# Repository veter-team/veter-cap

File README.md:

Veter CAP
=============

This is eagle files to produce veter cap.

Description
-------

Complete with additional library. Designed on EAGLE 6.3 Lite.

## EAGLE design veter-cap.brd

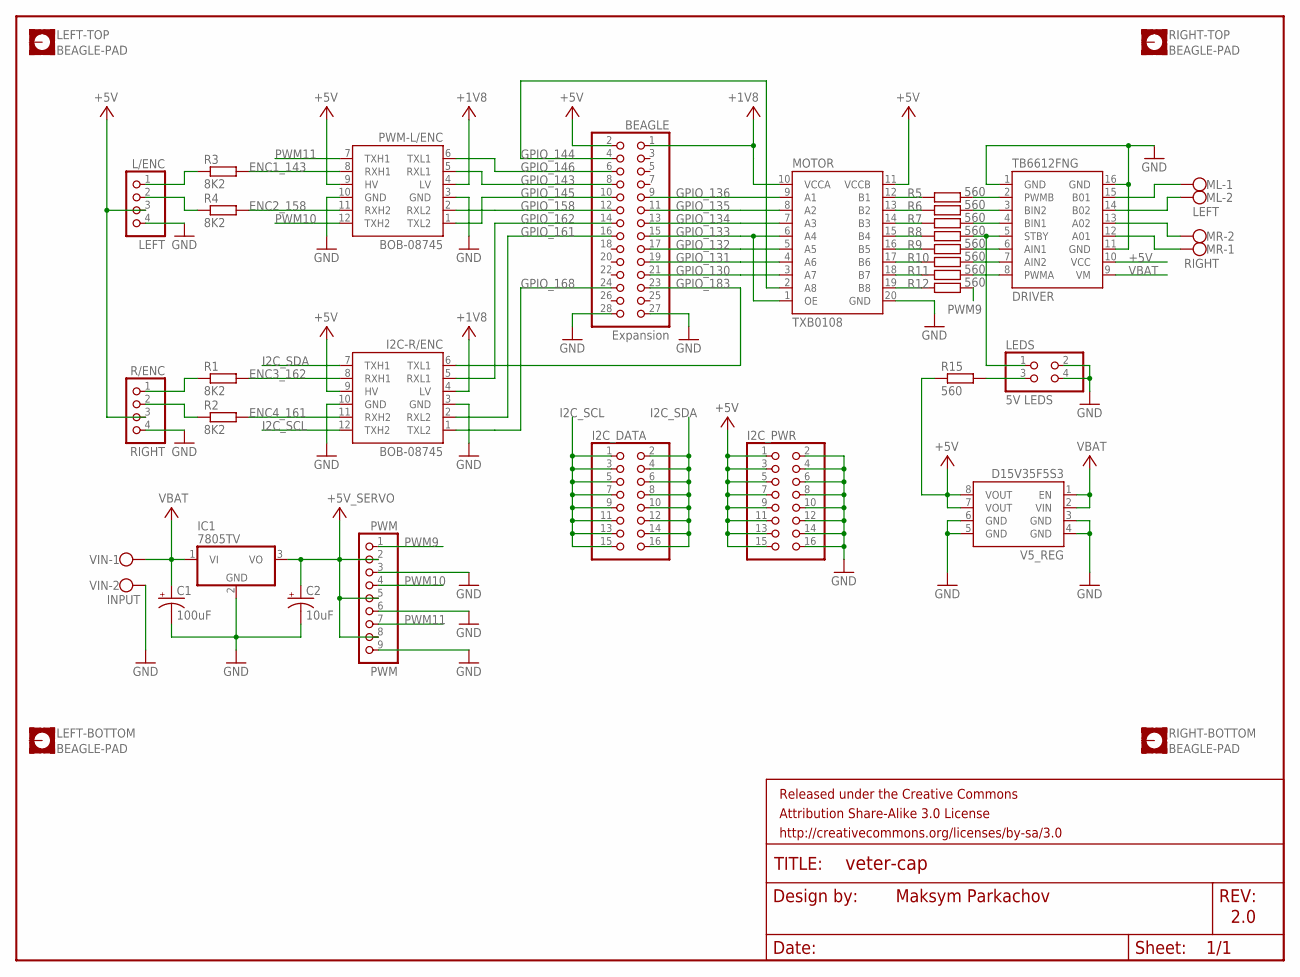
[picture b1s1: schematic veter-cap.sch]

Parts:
BEAGLE: Expansion; 2X14
C1: 100uF; CPOL-RADIAL-10UF-25V
C2: 10uF; CPOL-RADIAL-10UF-25V
DRIVER: TB6612FNG; 6612-BREAKOUT
FRAME1: FRAME-LETTER; CREATIVE_COMMONS
I2C-R/ENC: BOB-08745; BOB-08745-BREAKOUT
I2C_DATA, I2C_PWR: PINHD-2X8; 2X08
IC1: 7805TV; TO220V
L/ENC: LEFT; 1X04/90
LEDS: 5V LEDS; 2X02
LEFT-BOTTOM: BEAGLE-PAD
LEFT-TOP: BEAGLE-PAD
ML: LEFT; W237-102
MOTOR: TXB0108; TXB0108-BREAKOUT
MR: RIGHT; W237-102
PWM: PWM; 1X09/90
PWM-L/ENC: BOB-08745; BOB-08745-BREAKOUT
R1, R2, R3, R4: 8K2; 0207/10
R5, R6, R7, R8, R9, R10, R11, R12: 560; 0207/10
R15: 560; 0207/5V
R/ENC: RIGHT; 1X04/90
RIGHT-BOTTOM: BEAGLE-PAD
RIGHT-TOP: BEAGLE-PAD
V5_REG: D15V35F5S3; D15V35F5S3-BREAKOUT
VIN: INPUT; W237-102

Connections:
+1V8: BEAGLE.1, I2C-R/ENC.4 (LV), MOTOR.10 (VCCA), PWM-L/ENC.4 (LV)
+5V: BEAGLE.2, DRIVER.10 (VCC), I2C-R/ENC.9 (HV), I2C_PWR.1, I2C_PWR.3, I2C_PWR.5, I2C_PWR.7, I2C_PWR.9, I2C_PWR.11, I2C_PWR.13, I2C_PWR.15, L/ENC.3, MOTOR.11 (VCCB), PWM-L/ENC.9 (HV), R15.1, R/ENC.3, V5_REG.7 (VOUT), V5_REG.8 (VOUT)
+5V_SERVO: C2.1 (+), IC1.3 (VO), PWM.2, PWM.5, PWM.8
ENC1_143: PWM-L/ENC.8 (RXH1), R3.2
ENC2_158: PWM-L/ENC.11 (RXH2), R4.2
ENC3_162: I2C-R/ENC.8 (RXH1), R1.2
ENC4_161: I2C-R/ENC.11 (RXH2), R2.2
GND: BEAGLE.27, BEAGLE.28, C1.2 (-), C2.2 (-), DRIVER.1 (GND), DRIVER.11 (GND), DRIVER.16 (GND), I2C-R/ENC.3 (GND), I2C-R/ENC.10 (GND), I2C_PWR.2, I2C_PWR.4, I2C_PWR.6, I2C_PWR.8, I2C_PWR.10, I2C_PWR.12, I2C_PWR.14, I2C_PWR.16, IC1.2 (GND), L/ENC.4, LEDS.2, LEDS.4, MOTOR.20 (GND), PWM.3, PWM.6, PWM.9, PWM-L/ENC.3 (GND), PWM-L/ENC.10 (GND), R/ENC.4, V5_REG.3 (GND), V5_REG.4 (GND), V5_REG.5 (GND), V5_REG.6 (GND), VIN.2
GPIO_130: BEAGLE.21, MOTOR.3 (A7)
GPIO_131: BEAGLE.19, MOTOR.4 (A6)
GPIO_132: BEAGLE.17, MOTOR.5 (A5)
GPIO_133: BEAGLE.15, MOTOR.1 (OE), MOTOR.6 (A4)
GPIO_134: BEAGLE.13, MOTOR.7 (A3)
GPIO_135: BEAGLE.11, MOTOR.8 (A2)
GPIO_136: BEAGLE.9, MOTOR.9 (A1)
GPIO_143: BEAGLE.8, PWM-L/ENC.5 (RXL1)
GPIO_144: BEAGLE.4, MOTOR.2 (A8)
GPIO_145: BEAGLE.10, PWM-L/ENC.1 (TXL2)
GPIO_146: BEAGLE.6, PWM-L/ENC.6 (TXL1)
GPIO_158: BEAGLE.12, PWM-L/ENC.2 (RXL2)
GPIO_161: BEAGLE.16, I2C-R/ENC.2 (RXL2)
GPIO_162: BEAGLE.14, I2C-R/ENC.5 (RXL1)
GPIO_168: BEAGLE.24, I2C-R/ENC.1 (TXL2)
GPIO_183: BEAGLE.23, I2C-R/ENC.6 (TXL1)
I2C_SCL: I2C-R/ENC.12 (TXH2), I2C_DATA.1, I2C_DATA.3, I2C_DATA.5, I2C_DATA.7, I2C_DATA.9, I2C_DATA.11, I2C_DATA.13, I2C_DATA.15
I2C_SDA: I2C-R/ENC.7 (TXH1), I2C_DATA.2, I2C_DATA.4, I2C_DATA.6, I2C_DATA.8, I2C_DATA.10, I2C_DATA.12, I2C_DATA.14, I2C_DATA.16
unnamed: MOTOR.12 (B1), R5.1
unnamed: MOTOR.13 (B2), R6.1
unnamed: MOTOR.14 (B3), R7.1
unnamed: MOTOR.15 (B4), R8.1
unnamed: MOTOR.16 (B5), R9.1
unnamed: MOTOR.17 (B6), R10.1
unnamed: MOTOR.18 (B7), R11.1
unnamed: DRIVER.14 (B02), ML.2
unnamed: DRIVER.15 (B01), ML.1
unnamed: DRIVER.13 (A02), MR.2
unnamed: DRIVER.12 (A01), MR.1
unnamed: R1.1, R/ENC.1
unnamed: R2.1, R/ENC.2
unnamed: L/ENC.1, R3.1
unnamed: L/ENC.2, R4.1
unnamed: MOTOR.19 (B8), R12.1
unnamed: DRIVER.2 (PWMB), R5.2
unnamed: DRIVER.3 (BIN2), R6.2
unnamed: DRIVER.4 (BIN1), R7.2
unnamed: DRIVER.5 (STBY), LEDS.1, R8.2
unnamed: DRIVER.6 (AIN1), R9.2
unnamed: DRIVER.7 (AIN2), R10.2
unnamed: DRIVER.8 (PWMA), R11.2
unnamed: LEDS.3, R15.2
PWM9: PWM.1, R12.2
PWM10: PWM.4, PWM-L/ENC.12 (TXH2)
PWM11: PWM.7, PWM-L/ENC.7 (TXH1)
VBAT: C1.1 (+), DRIVER.9 (VM), IC1.1 (VI), V5_REG.1 (EN), V5_REG.2 (VIN), VIN.1

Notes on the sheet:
Maksym Parkachov
2.0

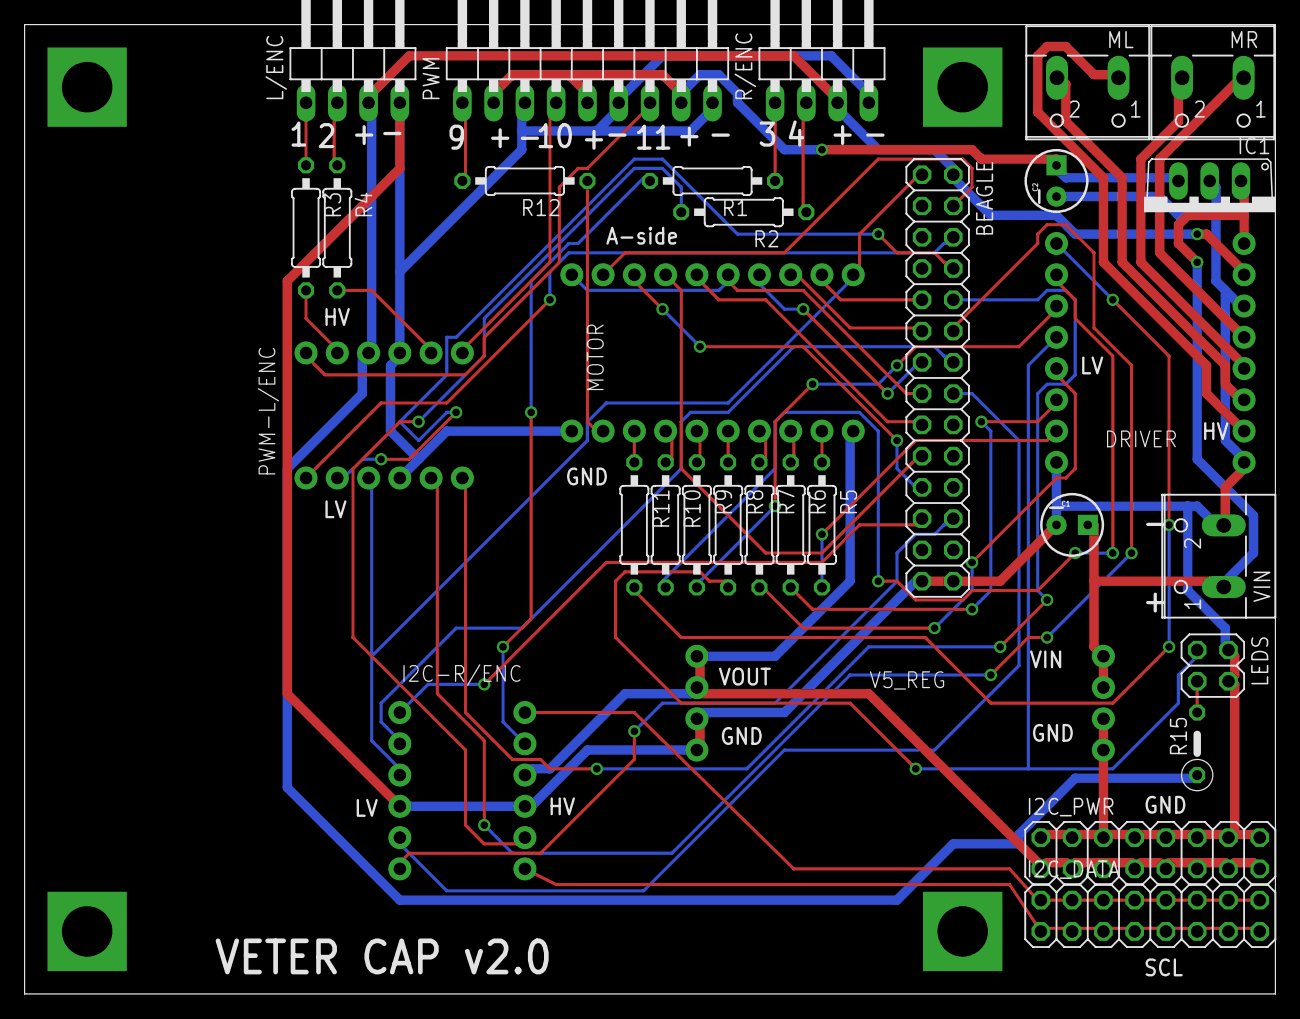
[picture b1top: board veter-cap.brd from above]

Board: 2 copper layers, 101.6 x 78.7 mm, 36 parts (0 on the bottom side), 54 nets.

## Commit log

2012-11-01 Intial version of the cap
2012-11-01 .DS_Store banished
2012-11-18 version 3.0 of the cap, fixed connector
2013-01-14 Add png schematic file for references

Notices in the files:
parts and their libraries:
SparkFun-Passives: Licensing: CC v3.0 Share-Alike You are welcome to use this library for commercial purposes.
SparkFun-Aesthetics: Released under the Creative Commons Attribution Share-Alike 3.0 License
SparkFun-Aesthetics: http://creativecommons.org/licenses/by-sa/3.0
